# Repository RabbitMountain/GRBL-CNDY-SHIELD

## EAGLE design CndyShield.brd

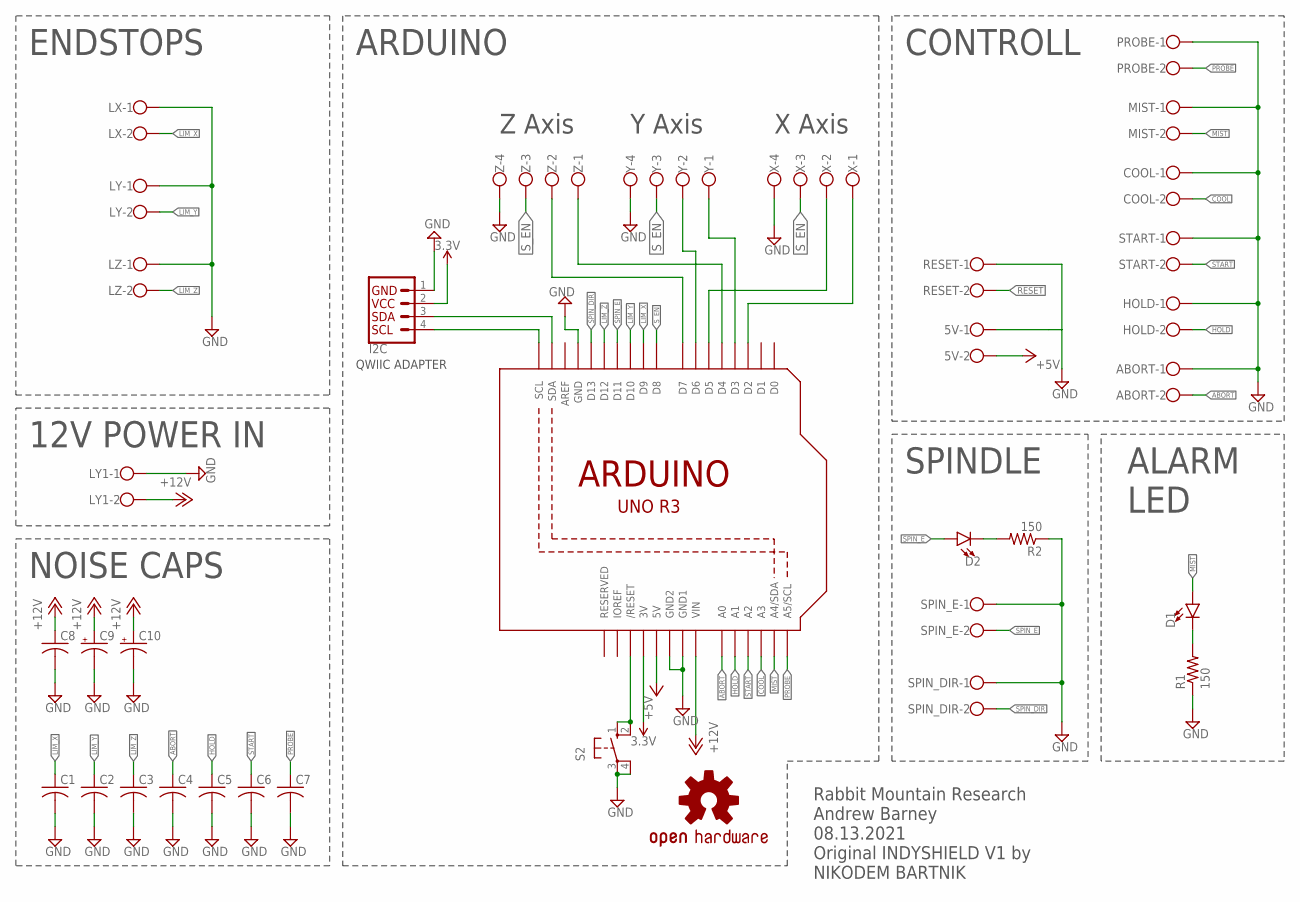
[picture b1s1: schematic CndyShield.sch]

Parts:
5V: W237-102
ABORT: W237-102
C1, C2, C3, C4, C5, C6, C7, C8: C-US025-024X044; C025-024X044
C9, C10: CPOL-USE1.8-4; E1,8-4
COOL: W237-102
D1, D2: LED5MM; LED_5MM
HOLD: W237-102
I2C: I2C_STANDARD; 1X04
LOGO1: OSHW-LOGOM; OSHW-LOGO-M
LX: W237-102
LY, LY1: W237-102
LZ: W237-102
MIST: W237-102
PROBE: W237-102
R1, R2: 150; 0207/10
RESET: W237-102
S2: 10-XX; B3F-10XX
SPIN_DIR: W237-102
SPIN_E: W237-102
START: W237-102
U1: ARDUINOR3-BPLACE
X: W237-4
Y: W237-4
Z: W237-4

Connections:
3.3V: I2C.2, U1.3V
+5V: 5V.2, U1.5V
+12V: C8.1, C9.+, C10.+, LY1.2, U1.VIN
ABORT: ABORT.2, C4.1, U1.A0
COOL: COOL.2, U1.A3
GND: 5V.1, ABORT.1, C1.2, C2.2, C3.2, C4.2, C5.2, C6.2, C7.2, C8.2, C9.-, C10.-, COOL.1, HOLD.1, I2C.1, LX.1, LY.1, LY1.1, LZ.1, MIST.1, PROBE.1, R1.1, R2.1, RESET.1, S2.3, S2.4 (P1), SPIN_DIR.1, SPIN_E.1, START.1, U1.GND, U1.GND1, U1.GND2, X.4, Y.4, Z.4
HOLD: C5.1, HOLD.2, U1.A1
LIM_X: C1.1, LX.2, U1.D9
LIM_Y: C2.1, LY.2, U1.D10
LIM_Z: C3.1, LZ.2, U1.D12
MIST: D1.A, MIST.2, U1.A4 (A4/SDA)
unnamed: U1.D5, X.2
unnamed: U1.D2, X.1
unnamed: U1.D6, Y.2
unnamed: U1.D3, Y.1
unnamed: U1.D7, Z.2
unnamed: U1.D4, Z.1
unnamed: D1.K (C), R1.2
unnamed: I2C.3, U1.SDA
unnamed: I2C.4, U1.SCL
unnamed: D2.K (C), R2.2
PROBE: C7.1, PROBE.2, U1.A5 (A5/SCL)
RESET: RESET.2, S2.1 (S), S2.2 (S1), U1.RESET (/RESET)
SPIN_DIR: SPIN_DIR.2, U1.D13
SPIN_E: D2.A, SPIN_E.2, U1.D11
START: C6.1, START.2, U1.A2
S_EN: U1.D8, X.3, Y.3, Z.3

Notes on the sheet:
X Axis
Y Axis
Z Axis
ENDSTOPS
SPINDLE
ARDUINO
12V POWER IN
Rabbit Mountain Research Andrew Barney 08.13.2021
QWIIC ADAPTER
Original INDYSHIELD V1 by NIKODEM BARTNIK
CONTROLL
NOISE CAPS
ALARM LED

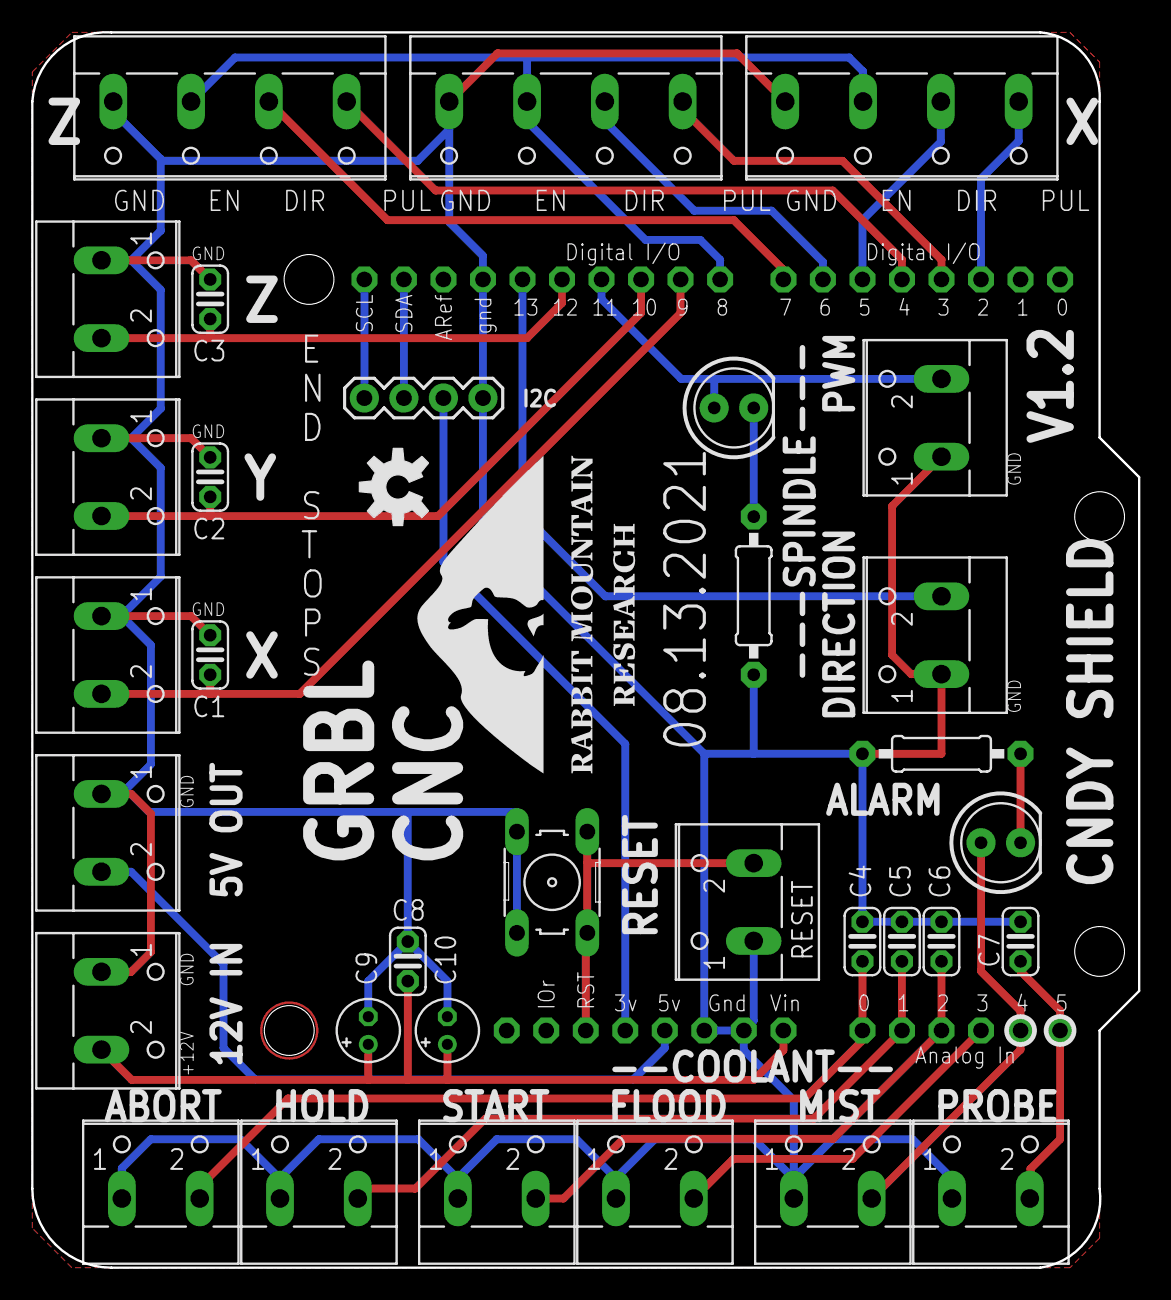
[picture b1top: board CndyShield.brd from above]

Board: 2 copper layers, 71.1 x 79.4 mm, 36 parts (0 on the bottom side), 27 nets.

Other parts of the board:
U$2: RMR-SIT-14MM

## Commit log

2021-08-03 Add files via upload
    V1.1 : remapped analog breakouts. Added filter capacitors. Added Alarm State LED on A4.
2021-08-05 Add files via upload
    minor silkscreen change for Analog 4. Changed LIGHT to MIST to be more consistent with official GRBL port use.
2021-08-08 Add files via upload
    V1.2: Fixed swapped silkscreen text for Spindle PWM and Spindle Direction. Added optional LED to Spindle PWM (pin 11) as an optional safety warning light.
2021-08-11 Add files via upload
    V1.3 Updated Silkscreen. Added OSHW Logo. Noise reduction caps.
2021-08-12 Add files via upload
    CN0DY Shield for GRBL V1.2. Ready for production. Fixed swapped silkscreen with spindle direction and spindle PWM. Added a number of new optional components. Added OSHW logo.
2021-08-13 Add files via upload
    Fixed unrouted air wires. fixed 3.2mm mounting holes.

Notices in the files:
parts and their libraries:
SparkFun-Connectors: Licensing: Creative Commons ShareAlike 4.0 International - https://creativecommons.org/licenses/by-sa/4.0
